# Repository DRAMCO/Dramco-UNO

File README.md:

# Dramco UNO

LoRaWAN-enabled Arduino board developed by [DRAMCO](https://www.dramco.be) featuring an accelerometer and a onewire connection optimized for low-power.

## Folder Structure

```
├───app
│   ├───Accelero-Test
│   ├───Dramco-UNO
│   └───Temprature-Sensor-Test
├───hardware
└───libraries
    └───arduino-lmic-master
```

- Example applications can be found in `app`
- Hardware folder includes the schematics 
- Altered libraries can be found in the `libraries`folder

## Description

- The device sends temperature, accelerometer and the battery level each MEASURE_INTERVAL.
- The (onewire) temperature sensor needs to be connected to the TEMP_BUS pin
- The (I2C) accelerometer with id ACC_ID is accessed through the Wire.h library
- The battery level is measured through the readVcc() function
- The measurements sent by the node are formatted with the Cayenne Low Power Payload (https://github.com/myDevicesIoT/cayenne-docs/blob/master/docs/LORA.md)

##  Dependencies:
- OneWire lib
- DallasTemperature lib
- Install arduino-lmic-master in lib folder of the Arduino IDE (for windows this is most likely here: C:\Program Files (x86)\Arduino\libraries)
    * If you do not use the lib provided in this repo, be sure to uncomment '#define DISABLE_JOIN' in src>lmic>config.h
- DeepSleepScheduler lib

- LoRaWAN keys see: https://www.thethingsnetwork.org/docs/devices/registration.html

## How to cite
```LaTex
@Misc{Dramco-UNO,
  author =   {B. Thoen and G. Leenders},
  title =    {{Dramco UNO}},
  howpublished  = "\url{https://github.com/DRAMCO/Dramco-UNO}",
  doi = {10.5281/zenodo.2476999}
}
```

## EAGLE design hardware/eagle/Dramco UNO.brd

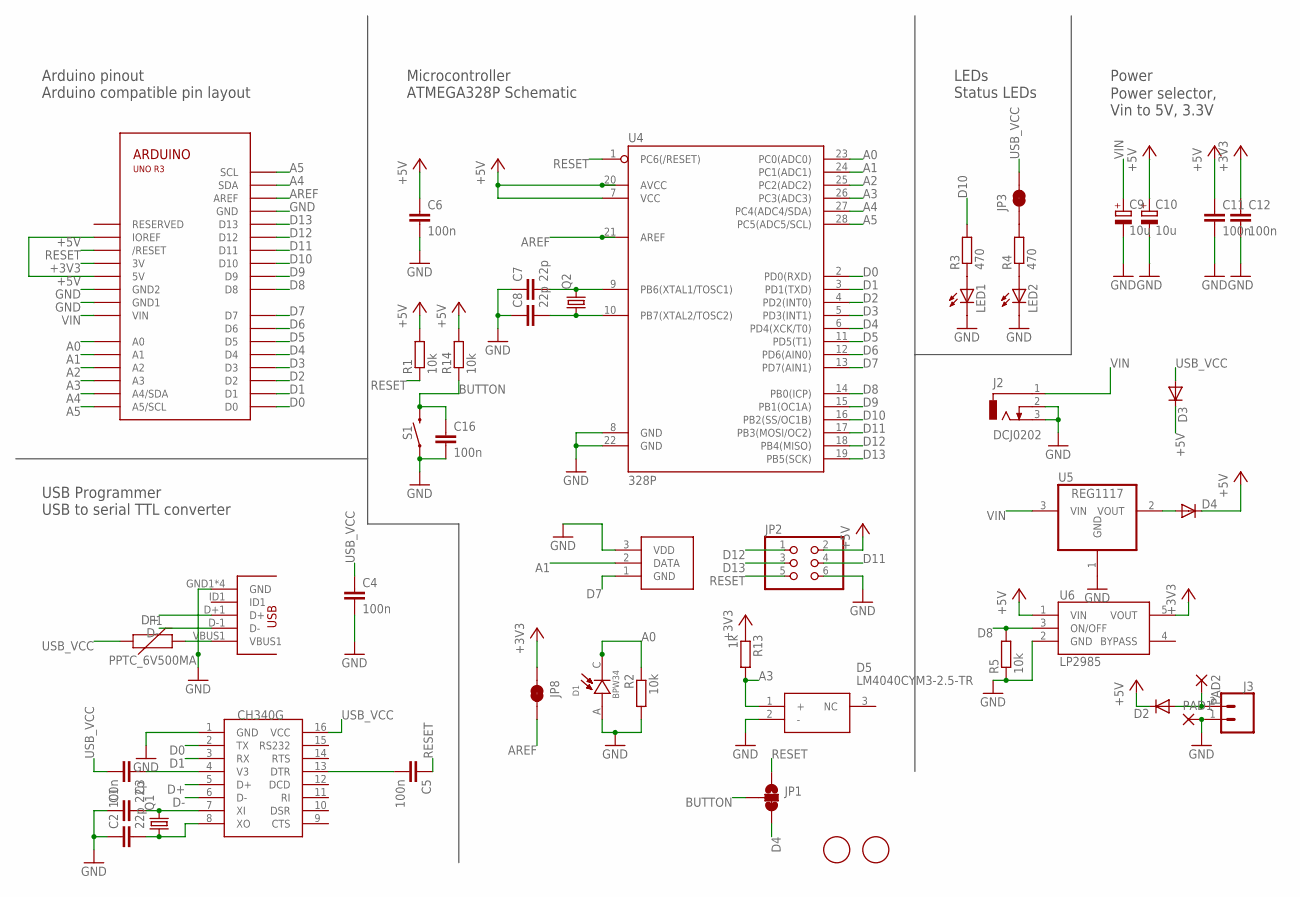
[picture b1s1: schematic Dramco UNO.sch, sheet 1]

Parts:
C1, C2, C7, C8: 22p; C025-024X044
C3, C4, C5, C11, C12, C16: 100n; C0603
C6: 100n; C025-024X044
C9, C10: 10u; E2-4
D1: BPW34; DIO_BPW34
D2, D3, D4: DIODE-D-5; D-5
D5: LM4040CYM3-2.5-TR; SOT95P235X111-3N
F1: PPTC_6V500MA; 0805
J1: USB-AB; USB-AB-MICRO-SMD_V02_BOSS
J2: DCJ0202
J3: CONN_02JST-PTH-2; JST-2-PTH
JP1: JUMPER-SMT_3_1-NC_TRACE_SILK; SMT-JUMPER_3_1-NC_TRACE_SILK
JP2: PINHD-2X3; 2X03
JP3, JP8: JUMPER-SMT_2_NC_TRACE_NO-SILK; SMT-JUMPER_2_NC_TRACE_NO-SILK
LED1, LED2: LED5MM
PAD1, PAD2: SMD2; SMD1,27-2,54
Q1, Q2: CRYSTALHC49S; HC49/S
R1, R2: 10k; 0204/7
R3, R4: 470; 0204/7
R5, R14: 10k; R0603
R13: 1k; R0603
S1: MOMENTARY-SWITCH-SPST-PTH-6.0MM; TACTILE_SWITCH_PTH_6.0MM
U1: ARDUINOR3-DIMENSION; ARDUINOR3
U2: CH340G; SOIC16
U3: DS18B20-TO92; TO92-
U4: 328P; DIP28
U5: REG1117; SOT223
U6: LP2985AIM5-3.3; SOT25
X1, X2: FIDUCIAL; FIDUCIAL_1MM

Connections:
+3V3: C12.1, JP8.1, R13.1, U1.3V, U6.5 (VOUT); also elsewhere on the board
+5V: C6.1, C10.+, C11.1, D2.C, D3.C, D4.C, JP2.2, R1.2, R14.2, U1.5V, U1.IOREF, U4.7 (VCC), U4.20 (AVCC), U6.1 (VIN); also elsewhere on the board
A0: D1.C, R2.1, U1.A0, U4.23 (PC0(ADC0))
A1: U1.A1, U3.2 (DATA), U4.24 (PC1(ADC1))
A2: U1.A2, U4.25 (PC2(ADC2))
A3: D5.1 (+), R13.2, U1.A3, U4.26 (PC3(ADC3))
A4: U1.A4 (A4/SDA), U1.SDA, U4.27 (PC4(ADC4/SDA)); also elsewhere on the board
A5: U1.A5 (A5/SCL), U1.SCL, U4.28 (PC5(ADC5/SCL)); also elsewhere on the board
AREF: JP8.2, U1.AREF, U4.21 (AREF)
BUTTON: C16.1, JP1.2, R14.1, S1.3 (2)
D0: U1.D0, U2.2 (TX), U4.2 (PD0(RXD))
D1: U1.D1, U2.3 (RX), U4.3 (PD1(TXD))
D2: U1.D2, U4.4 (PD2(INT0)); also elsewhere on the board
D3: U1.D3, U4.5 (PD3(INT1)); also elsewhere on the board
D4: JP1.3, U1.D4, U4.6 (PD4(XCK/T0)); also elsewhere on the board
D5: U1.D5, U4.11 (PD5(T1)); also elsewhere on the board
D6: U1.D6, U4.12 (PD6(AIN0)); also elsewhere on the board
D7: U1.D7, U3.1 (GND), U4.13 (PD7(AIN1))
D8: R5.2, U1.D8, U4.14 (PB0(ICP)), U6.3 (ON/OFF)
D9: U1.D9, U4.15 (PB1(OC1A)); also elsewhere on the board
D10: R3.2, U1.D10, U4.16 (PB2(SS/OC1B))
D11: JP2.4, U1.D11, U4.17 (PB3(MOSI/OC2)); also elsewhere on the board
D12: JP2.1, U1.D12, U4.18 (PB4(MISO)); also elsewhere on the board
D13: JP2.3, U1.D13, U4.19 (PB5(SCK)); also elsewhere on the board
D+: J1.D+1 (D+), U2.5 (D+)
D-: J1.D-1 (D-), U2.6 (D-)
GND: C1.1, C2.1, C4.2, C6.2, C7.1, C8.1, C9.-, C10.-, C11.2, C12.2, C16.2, D1.A, D5.2 (-), J1.GND1 (GND), J1.P$1 (GND), J1.P$2 (GND), J1.P$3 (GND), J2.2, J2.3, J3.1, JP2.6, LED1.K (C), LED2.K (C), PAD1.1, R2.2, R5.1, S1.1, U1.GND, U1.GND1, U1.GND2, U2.1 (GND), U3.3 (VDD), U4.8 (GND), U4.22 (GND), U5.1 (GND), U6.2 (GND); also elsewhere on the board
unnamed: C7.2, Q2.2, U4.9 (PB6(XTAL1/TOSC1))
unnamed: C8.2, Q2.1, U4.10 (PB7(XTAL2/TOSC2))
unnamed: C1.2, Q1.2, U2.7 (XI)
unnamed: C2.2, Q1.1, U2.8 (XO)
unnamed: C3.1, U2.4 (V3)
unnamed: LED1.A, R3.1
unnamed: LED2.A, R4.1
unnamed: C5.2, U2.13 (DTR)
unnamed: D4.A, U5.2 (VOUT)
unnamed: F1.2, J1.VBUS1
unnamed: JP3.1, R4.2
RESET: C5.1, JP1.1, JP2.5, R1.1, U1.RESET (/RESET), U4.1 (PC6(/RESET))
USB_VCC: C3.2, C4.1, D3.A, F1.1, JP3.2, U2.16 (VCC)
VBAT: D2.A, J3.2, PAD2.1
VIN: C9.+, J2.1, U1.VIN, U5.3 (VIN)

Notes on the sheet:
Arduino pinout
Arduino compatible pin layout
Microcontroller
ATMEGA328P Schematic
USB Programmer
USB to serial TTL converter
LEDs
Status LEDs
Power
Power selector, Vin to 5V, 3.3V

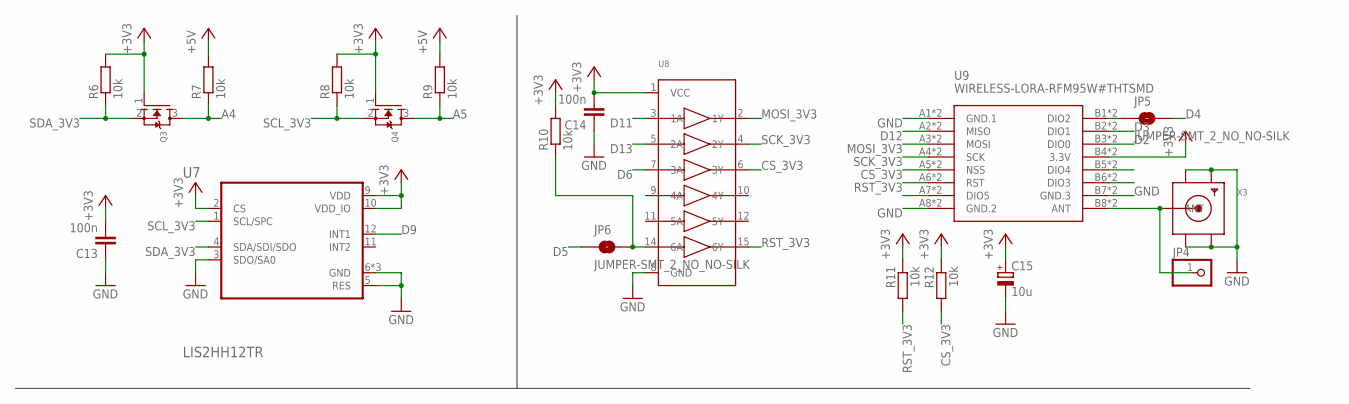
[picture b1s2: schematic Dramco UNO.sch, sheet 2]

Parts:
C13, C14: 100n; C0603
C15: 10u; E2-4
JP4: PINHD-1X1; 1X01
JP5, JP6: JUMPER-SMT_2_NO_NO-SILK; SMT-JUMPER_2_NO_NO-SILK
Q3, Q4: MOSFET-NREFLOW; SOT23
R6, R7, R8, R9, R10: 10k; R0603
R11, R12: 10k; 0204/7
U7: LIS2HH12TR; PQFN50P200X200X100-12N
U8: 74HC4050DTSSOP; TSSOP16
U9: WIRELESS-LORA-RFM95W#THTSMD
X3: SMACONNECTOR_EDGE_UFL; SMA_EDGELAUNCH_UFL

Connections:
+3V3: C13.2, C14.2, C15.+, Q3.1 (G), Q4.1 (G), R6.2, R8.2, R10.2, R11.1, R12.1, U7.2 (CS), U7.9 (VDD), U7.10 (VDD_IO), U8.1 (VCC), U9.B4 (3.3V), U9.B12 (3.3V); also elsewhere on the board
+5V: R7.2, R9.2; also elsewhere on the board
A4: Q3.3 (D), R7.1; also elsewhere on the board
A5: Q4.3 (D), R9.1; also elsewhere on the board
CS_3V3: R12.2, U8.6 (3Y), U9.A5 (NSS), U9.A13 (NSS)
D2: U9.B3 (DIO0), U9.B11 (DIO0); also elsewhere on the board
D3: U9.B2 (DIO1), U9.B10 (DIO1); also elsewhere on the board
D4: JP5.2; also elsewhere on the board
D5: JP6.1; also elsewhere on the board
D6: U8.7 (3A); also elsewhere on the board
D9: U7.12 (INT1); also elsewhere on the board
D11: U8.3 (1A); also elsewhere on the board
D12: U9.A2 (MISO), U9.A10 (MISO); also elsewhere on the board
D13: U8.5 (2A); also elsewhere on the board
GND: C13.1, C14.1, C15.-, U7.3 (SDO/SA0), U7.5 (RES), U7.6 (GND), U7.7 (GND), U7.8 (GND), U8.8 (GND), U9.A1 (GND.1), U9.A8 (GND.2), U9.A9 (GND.1), U9.A16 (GND.2), U9.B7 (GND.3), U9.B15 (GND.3), X3.GND@1 (GND1), X3.GND@2 (GND2), X3.GND@3 (GND3), X3.GND@4 (GND4); also elsewhere on the board
MOSI_3V3: U8.2 (1Y), U9.A3 (MOSI), U9.A11 (MOSI)
unnamed: JP4.1, U9.B8 (ANT), U9.B16 (ANT), X3.P (ANT)
unnamed: JP5.1, U9.B1 (DIO2), U9.B9 (DIO2)
unnamed: JP6.2, R10.1, U8.14 (6A)
unnamed: U9.A7 (DIO5), U9.A15 (DIO5)
unnamed: U9.B5 (DIO4), U9.B13 (DIO4)
unnamed: U9.B6 (DIO3), U9.B14 (DIO3)
RST_3V3: R11.2, U8.15 (6Y), U9.A6 (RST), U9.A14 (RST)
SCK_3V3: U8.4 (2Y), U9.A4 (SCK), U9.A12 (SCK)
SCL_3V3: Q4.2 (S), R8.1, U7.1 (SCL/SPC)
SDA_3V3: Q3.2 (S), R6.1, U7.4 (SDA/SDI/SDO)

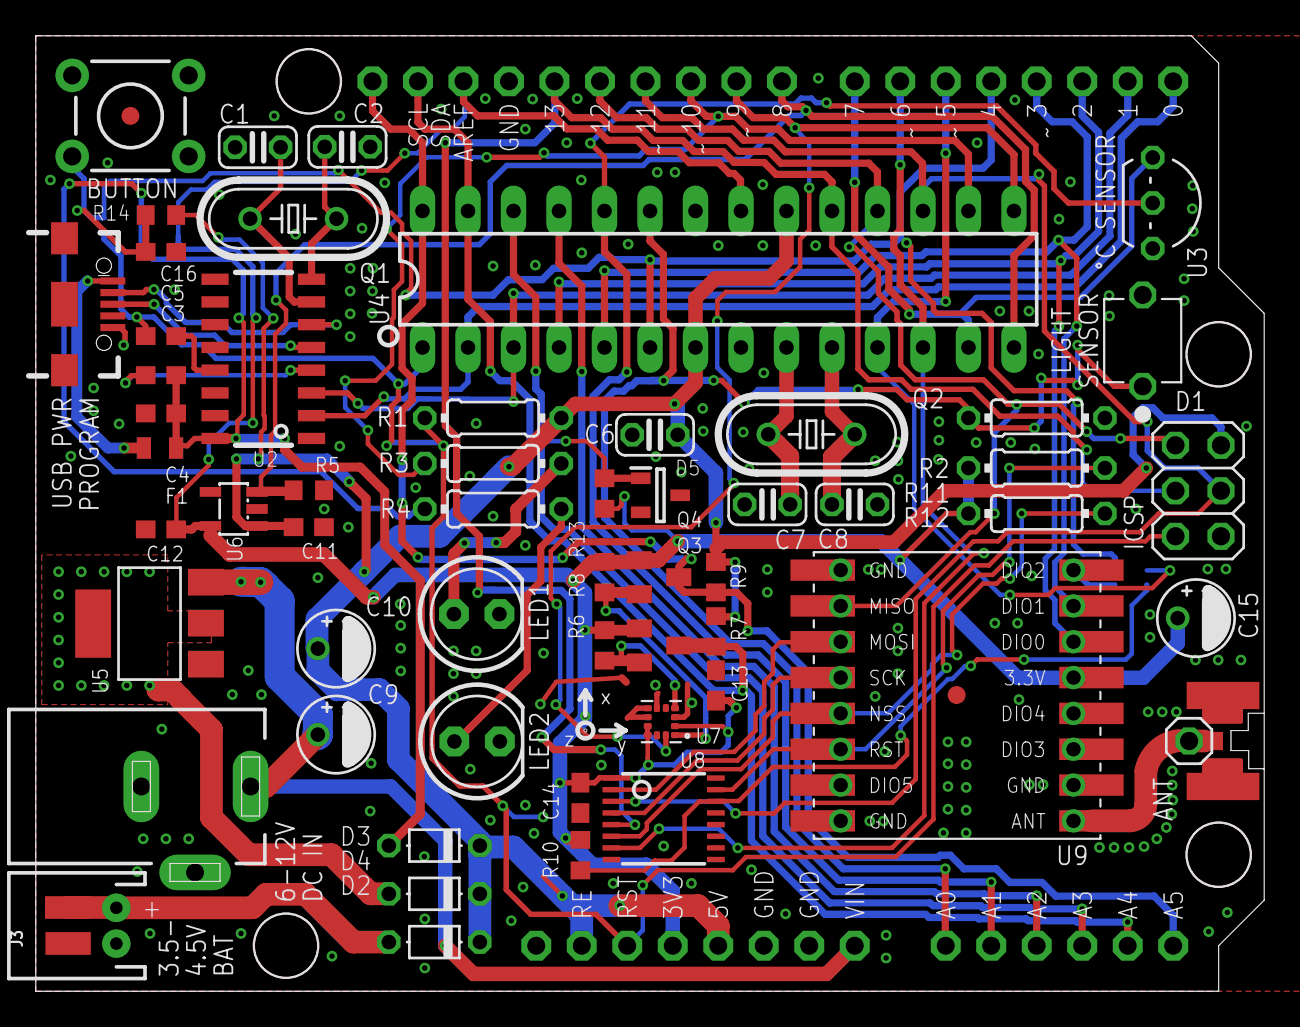
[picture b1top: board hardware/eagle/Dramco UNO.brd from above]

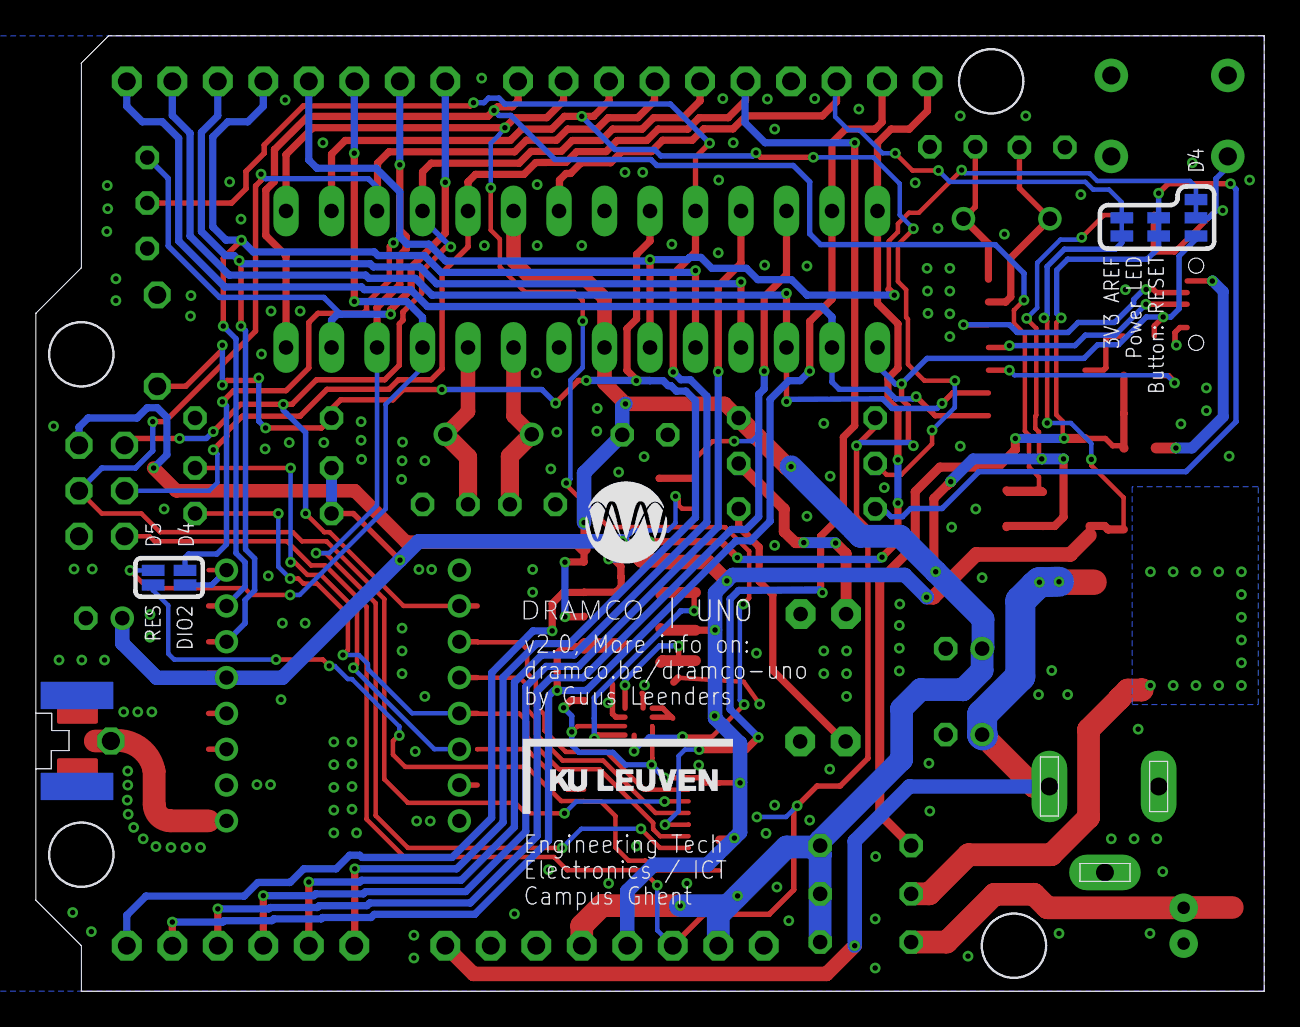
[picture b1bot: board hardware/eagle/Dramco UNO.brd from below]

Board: 2 copper layers, 68.5 x 53.2 mm, 67 parts (5 on the bottom side), 54 nets.

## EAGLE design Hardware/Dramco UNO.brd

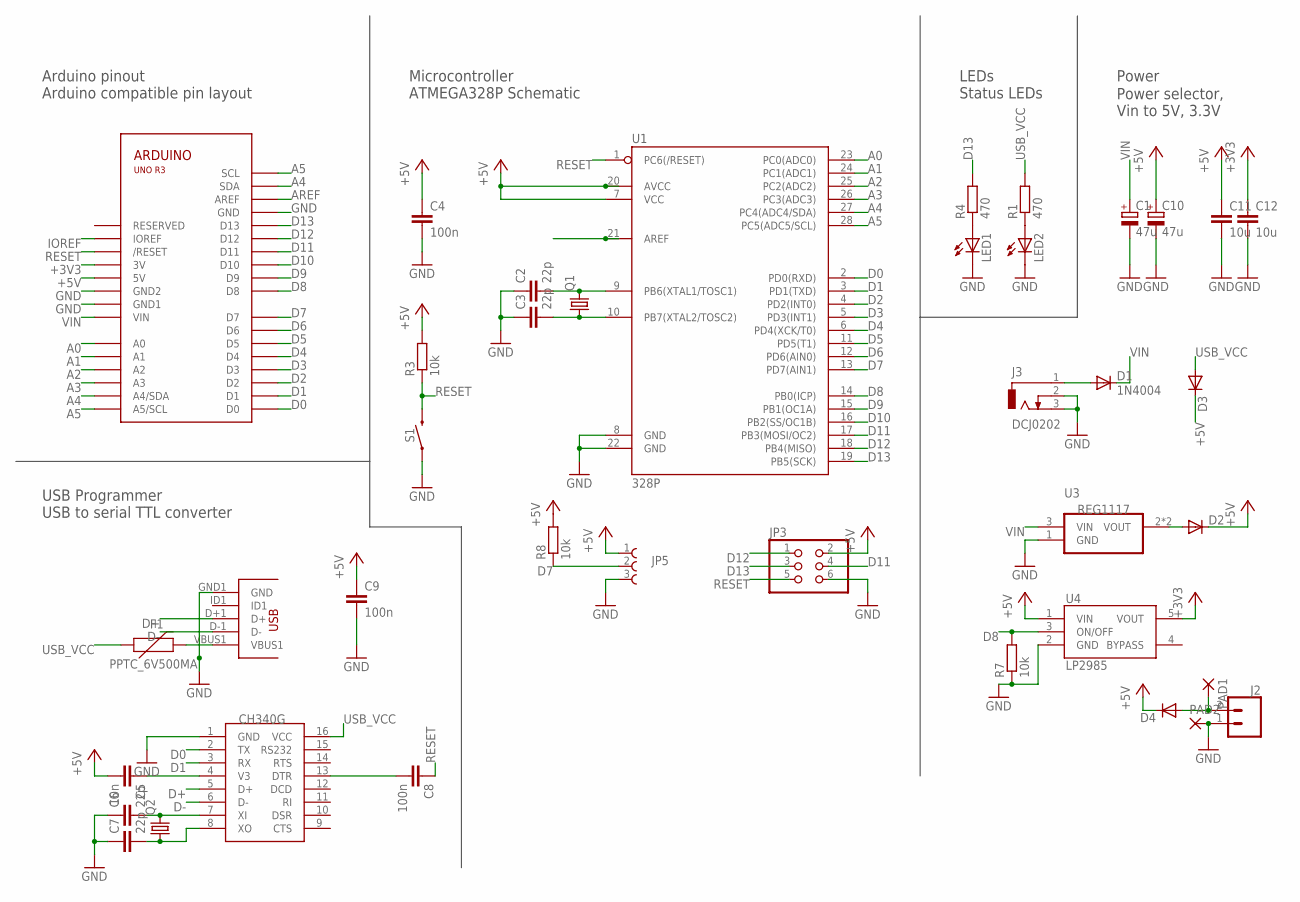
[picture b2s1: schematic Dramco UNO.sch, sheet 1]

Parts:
C1, C10: 47u; E2,5-6
C2, C3: 22p; C025-024X044
C4: 100n; C025-024X044
C5: 10n; C0603
C6, C7: 22p; C0603
C8, C9: 100n; C0603
C11, C12: 10u; C0603
D1: 1N4004; DO41-10
D2, D3, D4: DIODE-SOD123; SOD123
F1: PPTC_6V500MA; 0805
J1: USB-AB; USB-AB-MICRO-SMD_V02_BOSS
J2: CONN_02JST-PTH-2; JST-2-PTH
J3: DCJ0202
JP1: ARDUINOR3-DIMENSION; ARDUINOR3
JP3: PINHD-2X3; 2X03
JP5: 691210910003
LED1, LED2: LED5MM
PAD1, PAD2: SMD2; SMD1,27-2,54
Q1, Q2: CRYSTALHC49S; HC49/S
R1, R4: 470; 0204/7
R3, R8: 10k; 0204/7
R7: 10k; R0603
S1: MOMENTARY-SWITCH-SPST-PTH-6.0MM; TACTILE_SWITCH_PTH_6.0MM
U1: 328P; DIP28
U2: CH340G; SOIC16
U3: REG1117; SOT223
U4: LP2985AIM5-3.3; SOT25

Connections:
+3V3: C12.1, JP1.3V, U4.5 (VOUT); also elsewhere on the board
+5V: C4.1, C5.2, C9.1, C10.+, C11.1, D2.C, D3.C, D4.C, JP1.5V, JP3.2, JP5.1, R3.2, R8.2, U1.7 (VCC), U1.20 (AVCC), U4.1 (VIN); also elsewhere on the board
A0: JP1.A0, U1.23 (PC0(ADC0))
A1: JP1.A1, U1.24 (PC1(ADC1))
A2: JP1.A2, U1.25 (PC2(ADC2))
A3: JP1.A3, U1.26 (PC3(ADC3))
A4: JP1.A4 (A4/SDA), JP1.SDA, U1.27 (PC4(ADC4/SDA)); also elsewhere on the board
A5: JP1.A5 (A5/SCL), JP1.SCL, U1.28 (PC5(ADC5/SCL)); also elsewhere on the board
AREF: JP1.AREF, U1.21 (AREF)
D0: JP1.D0, U1.2 (PD0(RXD)), U2.2 (TX)
D1: JP1.D1, U1.3 (PD1(TXD)), U2.3 (RX)
D2: JP1.D2, U1.4 (PD2(INT0)); also elsewhere on the board
D3: JP1.D3, U1.5 (PD3(INT1)); also elsewhere on the board
D4: JP1.D4, U1.6 (PD4(XCK/T0)); also elsewhere on the board
D5: JP1.D5, U1.11 (PD5(T1)); also elsewhere on the board
D6: JP1.D6, U1.12 (PD6(AIN0)); also elsewhere on the board
D7: JP1.D7, JP5.2, R8.1, U1.13 (PD7(AIN1))
D8: JP1.D8, R7.2, U1.14 (PB0(ICP)), U4.3 (ON/OFF)
D9: JP1.D9, U1.15 (PB1(OC1A)); also elsewhere on the board
D10: JP1.D10, U1.16 (PB2(SS/OC1B))
D11: JP1.D11, JP3.4, U1.17 (PB3(MOSI/OC2)); also elsewhere on the board
D12: JP1.D12, JP3.1, U1.18 (PB4(MISO)); also elsewhere on the board
D13: JP1.D13, JP3.3, R4.2, U1.19 (PB5(SCK)); also elsewhere on the board
D+: J1.D+1 (D+), U2.5 (D+)
D-: J1.D-1 (D-), U2.6 (D-)
GND: C1.-, C2.1, C3.1, C4.2, C6.1, C7.1, C9.2, C10.-, C11.2, C12.2, J1.GND1 (GND), J2.1, J3.2, J3.3, JP1.GND, JP1.GND1, JP1.GND2, JP3.6, JP5.3, LED1.K (C), LED2.K (C), PAD2.1, R7.1, S1.1, U1.8 (GND), U1.22 (GND), U2.1 (GND), U3.1 (GND), U4.2 (GND); also elsewhere on the board
IOREF: JP1.IOREF
unnamed: C2.2, Q1.2, U1.9 (PB6(XTAL1/TOSC1))
unnamed: C3.2, Q1.1, U1.10 (PB7(XTAL2/TOSC2))
unnamed: C6.2, Q2.2, U2.7 (XI)
unnamed: C7.2, Q2.1, U2.8 (XO)
unnamed: C5.1, U2.4 (V3)
unnamed: LED1.A, R4.1
unnamed: LED2.A, R1.1
unnamed: C8.2, U2.13 (DTR)
unnamed: D2.A, U3.2 (VOUT), U3.4 (VOUT)
unnamed: F1.2, J1.VBUS1
unnamed: D1.A, J3.1
RESET: C8.1, JP1.RESET (/RESET), JP3.5, R3.1, S1.3 (2), U1.1 (PC6(/RESET))
USB_VCC: D3.A, F1.1, R1.2, U2.16 (VCC)
VBAT: D4.A, J2.2, PAD1.1
VIN: C1.+, D1.C, JP1.VIN, U3.3 (VIN)

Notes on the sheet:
Arduino pinout
Arduino compatible pin layout
Microcontroller
ATMEGA328P Schematic
USB Programmer
USB to serial TTL converter
LEDs
Status LEDs
Power
Power selector, Vin to 5V, 3.3V

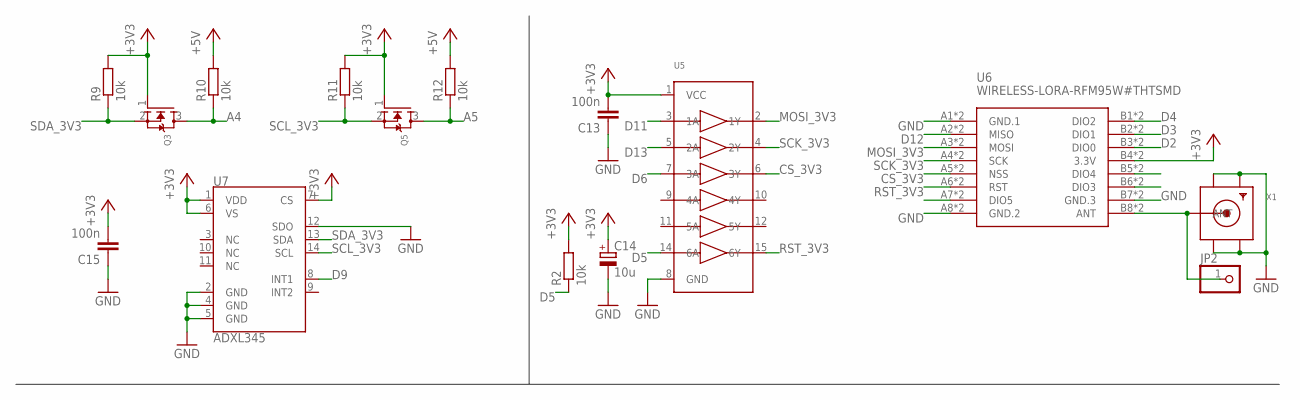
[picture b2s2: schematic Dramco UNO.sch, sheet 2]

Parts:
C13, C15: 100n; C0603
C14: 10u; E2-4
JP2: PINHD-1X1; 1X01
Q3, Q5: MOSFET-NREFLOW; SOT23
R2, R9, R10, R11, R12: 10k; R0603
U5: 74HC4050DTSSOP; TSSOP16
U6: WIRELESS-LORA-RFM95W#THTSMD
U7: ADXL345; LGA-14
X1: SMACONNECTOR_EDGE_UFL; SMA_EDGELAUNCH_UFL

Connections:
+3V3: C13.2, C14.+, C15.2, Q3.1 (G), Q5.1 (G), R2.2, R9.2, R11.2, U5.1 (VCC), U6.B4 (3.3V), U6.B12 (3.3V), U7.1 (VDD), U7.6 (VS), U7.7 (CS); also elsewhere on the board
+5V: R10.2, R12.2; also elsewhere on the board
A4: Q3.3 (D), R10.1; also elsewhere on the board
A5: Q5.3 (D), R12.1; also elsewhere on the board
CS_3V3: U5.6 (3Y), U6.A5 (NSS), U6.A13 (NSS)
D2: U6.B3 (DIO0), U6.B11 (DIO0); also elsewhere on the board
D3: U6.B2 (DIO1), U6.B10 (DIO1); also elsewhere on the board
D4: U6.B1 (DIO2), U6.B9 (DIO2); also elsewhere on the board
D5: R2.1, U5.14 (6A); also elsewhere on the board
D6: U5.7 (3A); also elsewhere on the board
D9: U7.8 (INT1); also elsewhere on the board
D11: U5.3 (1A); also elsewhere on the board
D12: U6.A2 (MISO), U6.A10 (MISO); also elsewhere on the board
D13: U5.5 (2A); also elsewhere on the board
GND: C13.1, C14.-, C15.1, U5.8 (GND), U6.A1 (GND.1), U6.A8 (GND.2), U6.A9 (GND.1), U6.A16 (GND.2), U6.B7 (GND.3), U6.B15 (GND.3), U7.2 (GND), U7.4 (GND), U7.5 (GND), U7.12 (SDO), X1.GND@1 (GND1), X1.GND@2 (GND2), X1.GND@3 (GND3), X1.GND@4 (GND4); also elsewhere on the board
MOSI_3V3: U5.2 (1Y), U6.A3 (MOSI), U6.A11 (MOSI)
unnamed: JP2.1, U6.B8 (ANT), U6.B16 (ANT), X1.P (ANT)
unnamed: U6.A7 (DIO5), U6.A15 (DIO5)
unnamed: U6.B5 (DIO4), U6.B13 (DIO4)
unnamed: U6.B6 (DIO3), U6.B14 (DIO3)
RST_3V3: U5.15 (6Y), U6.A6 (RST), U6.A14 (RST)
SCK_3V3: U5.4 (2Y), U6.A4 (SCK), U6.A12 (SCK)
SCL_3V3: Q5.2 (S), R11.1, U7.14 (SCL)
SDA_3V3: Q3.2 (S), R9.1, U7.13 (SDA)

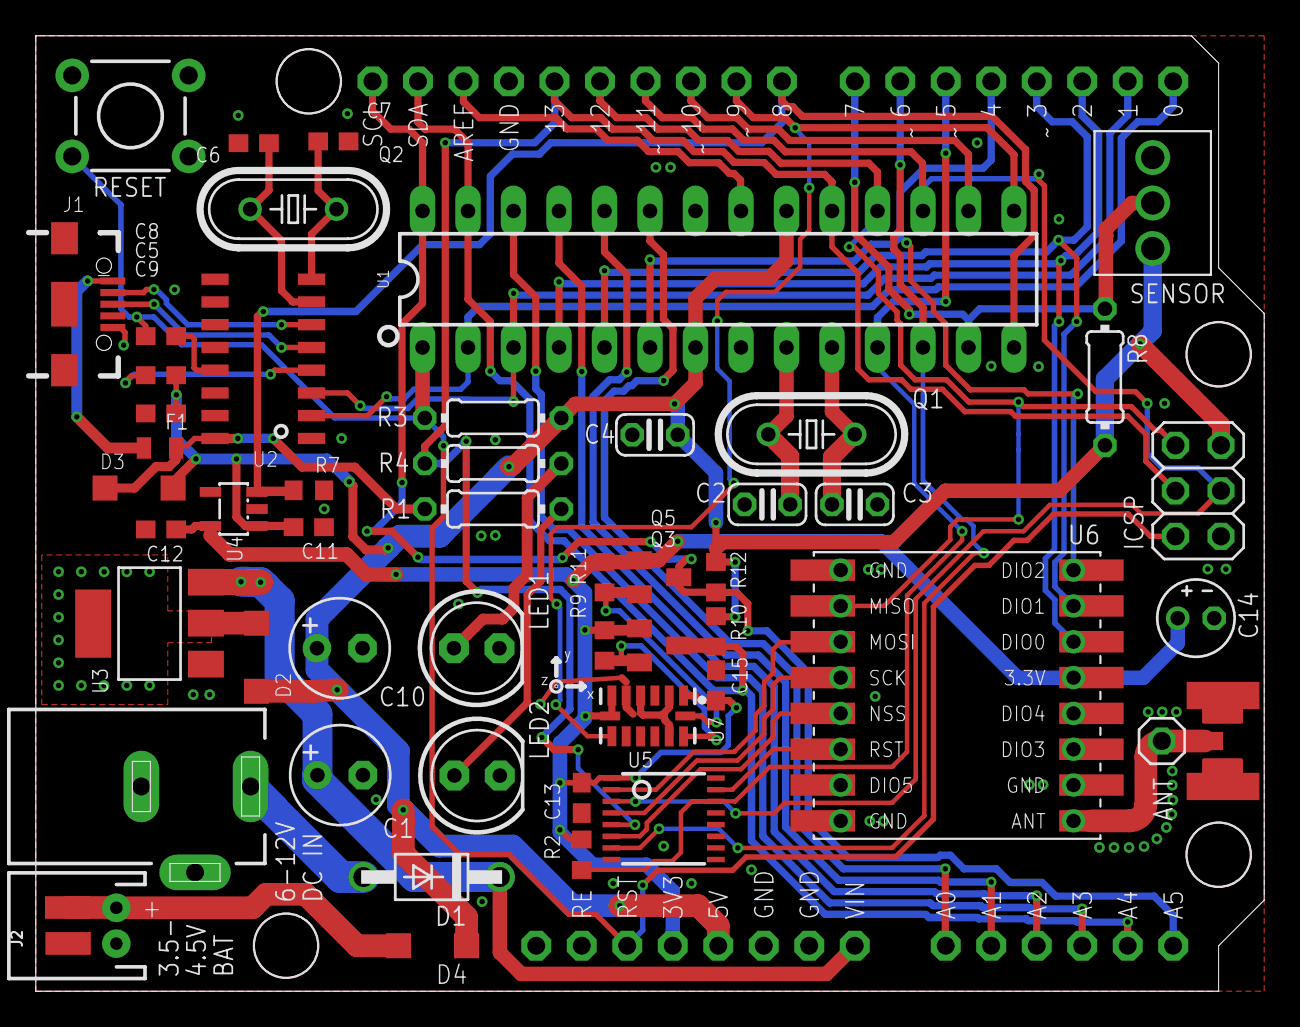
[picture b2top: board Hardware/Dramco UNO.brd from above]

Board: 2 copper layers, 68.5 x 53.2 mm, 54 parts (0 on the bottom side), 51 nets.

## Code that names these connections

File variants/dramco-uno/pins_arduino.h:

/*
  pins_arduino.h - Pin definition functions for Arduino
  Part of Arduino - http://www.arduino.cc/

  Copyright (c) 2007 David A. Mellis

  This library is free software; you can redistribute it and/or
  modify it under the terms of the GNU Lesser General Public
  License as published by the Free Software Foundation; either
  version 2.1 of the License, or (at your option) any later version.

  This library is distributed in the hope that it will be useful,
  but WITHOUT ANY WARRANTY; without even the implied warranty of
  MERCHANTABILITY or FITNESS FOR A PARTICULAR PURPOSE.  See the GNU
  Lesser General Public License for more details.

  You should have received a copy of the GNU Lesser General
  Public License along with this library; if not, write to the
  Free Software Foundation, Inc., 59 Temple Place, Suite 330,
  Boston, MA  02111-1307  USA
*/

#ifndef Pins_Arduino_h
#define Pins_Arduino_h

#include <avr/pgmspace.h>

#define NUM_DIGITAL_PINS            20
#define NUM_ANALOG_INPUTS           6
#define analogInputToDigitalPin(p)  ((p < 6) ? (p) + 14 : -1)

#if defined(__AVR_ATmega8__)
#define digitalPinHasPWM(p)         ((p) == 9 || (p) == 10 || (p) == 11)
#else
#define digitalPinHasPWM(p)         ((p) == 3 || (p) == 5 || (p) == 6 || (p) == 9 || (p) == 10 || (p) == 11)
#endif

#define PIN_SPI_SS    (10)
#define PIN_SPI_MOSI  (11)
#define PIN_SPI_MISO  (12)
#define PIN_SPI_SCK   (13)

static const uint8_t SS   = PIN_SPI_SS;
static const uint8_t MOSI = PIN_SPI_MOSI;
static const uint8_t MISO = PIN_SPI_MISO;
static const uint8_t SCK  = PIN_SPI_SCK;

#define PIN_WIRE_SDA        (18)
#define PIN_WIRE_SCL        (19)

static const uint8_t SDA = PIN_WIRE_SDA;
static const uint8_t SCL = PIN_WIRE_SCL;

#if HARDWARE_VERSION >= 2
#define LED_BUILTIN 10
#else
#define LED_BUILTIN 4
#endif

#define PIN_A0   (14)
#define PIN_A1   (15)
#define PIN_A2   (16)
#define PIN_A3   (17)
#define PIN_A4   (18)
#define PIN_A5   (19)
#define PIN_A6   (20)
#define PIN_A7   (21)

static const uint8_t A0 = PIN_A0;
static const uint8_t A1 = PIN_A1;
static const uint8_t A2 = PIN_A2;
static const uint8_t A3 = PIN_A3;
static const uint8_t A4 = PIN_A4;
static const uint8_t A5 = PIN_A5;
static const uint8_t A6 = PIN_A6;
static const uint8_t A7 = PIN_A7;

#define digitalPinToPCICR(p)    (((p) >= 0 && (p) <= 21) ? (&PCICR) : ((uint8_t *)0))
#define digitalPinToPCICRbit(p) (((p) <= 7) ? 2 : (((p) <= 13) ? 0 : 1))
#define digitalPinToPCMSK(p)    (((p) <= 7) ? (&PCMSK2) : (((p) <= 13) ? (&PCMSK0) : (((p) <= 21) ? (&PCMSK1) : ((uint8_t *)0))))
#define digitalPinToPCMSKbit(p) (((p) <= 7) ? (p) : (((p) <= 13) ? ((p) - 8) : ((p) - 14)))

#define digitalPinToInterrupt(p)  ((p) == 2 ? 0 : ((p) == 3 ? 1 : NOT_AN_INTERRUPT))

#ifdef ARDUINO_MAIN

// On the Arduino board, digital pins are also used
// for the analog output (software PWM).  Analog input
// pins are a separate set.

// ATMEL ATMEGA8 & 168 / ARDUINO
//
//                  +-\/-+
//            PC6  1|    |28  PC5 (AI 5)
//      (D 0) PD0  2|    |27  PC4 (AI 4)
//      (D 1) PD1  3|    |26  PC3 (AI 3)
//      (D 2) PD2  4|    |25  PC2 (AI 2)
// PWM+ (D 3) PD3  5|    |24  PC1 (AI 1)
//      (D 4) PD4  6|    |23  PC0 (AI 0)
//            VCC  7|    |22  GND
//            GND  8|    |21  AREF
//            PB6  9|    |20  AVCC
//            PB7 10|    |19  PB5 (D 13)
// PWM+ (D 5) PD5 11|    |18  PB4 (D 12)
// PWM+ (D 6) PD6 12|    |17  PB3 (D 11) PWM
//      (D 7) PD7 13|    |16  PB2 (D 10) PWM
//      (D 8) PB0 14|    |15  PB1 (D 9) PWM
//                  +----+
//
// (PWM+ indicates the additional PWM pins on the ATmega168.)

// ATMEL ATMEGA1280 / ARDUINO
//
// 0-7 PE0-PE7   works
// 8-13 PB0-PB5  works
// 14-21 PA0-PA7 works 
// 22-29 PH0-PH7 works
// 30-35 PG5-PG0 works
// 36-43 PC7-PC0 works
// 44-51 PJ7-PJ0 works
// 52-59 PL7-PL0 works
// 60-67 PD7-PD0 works
// A0-A7 PF0-PF7
// A8-A15 PK0-PK7


// these arrays map port names (e.g. port B) to the
// appropriate addresses for various functions (e.g. reading
// and writing)
const uint16_t PROGMEM port_to_mode_PGM[] = {
	NOT_A_PORT,
	NOT_A_PORT,
	(uint16_t) &DDRB,
	(uint16_t) &DDRC,
	(uint16_t) &DDRD,
};

const uint16_t PROGMEM port_to_output_PGM[] = {
	NOT_A_PORT,
	NOT_A_PORT,
	(uint16_t) &PORTB,
	(uint16_t) &PORTC,
	(uint16_t) &PORTD,
};

const uint16_t PROGMEM port_to_input_PGM[] = {
	NOT_A_PORT,
	NOT_A_PORT,
	(uint16_t) &PINB,
	(uint16_t) &PINC,
	(uint16_t) &PIND,
};

const uint8_t PROGMEM digital_pin_to_port_PGM[] = {
	PD, /* 0 */
	PD,
	PD,
	PD,
	PD,
	PD,
	PD,
	PD,
	PB, /* 8 */
	PB,
	PB,
	PB,
	PB,
	PB,
	PC, /* 14 */
	PC,
	PC,
	PC,
	PC,
	PC,
};

const uint8_t PROGMEM digital_pin_to_bit_mask_PGM[] = {
	_BV(0), /* 0, port D */
	_BV(1),
	_BV(2),
	_BV(3),
	_BV(4),
	_BV(5),
	_BV(6),
	_BV(7),
	_BV(0), /* 8, port B */
	_BV(1),
	_BV(2),
	_BV(3),
	_BV(4),
	_BV(5),
	_BV(0), /* 14, port C */
	_BV(1),
	_BV(2),
	_BV(3),
	_BV(4),
	_BV(5),
};

const uint8_t PROGMEM digital_pin_to_timer_PGM[] = {
	NOT_ON_TIMER, /* 0 - port D */
	NOT_ON_TIMER,
	NOT_ON_TIMER,
	// on the ATmega168, digital pin 3 has hardware pwm
#if defined(__AVR_ATmega8__)
	NOT_ON_TIMER,
#else
	TIMER2B,
#endif
	NOT_ON_TIMER,
	// on the ATmega168, digital pins 5 and 6 have hardware pwm
#if defined(__AVR_ATmega8__)
	NOT_ON_TIMER,
	NOT_ON_TIMER,
#else
	TIMER0B,
	TIMER0A,
#endif
	NOT_ON_TIMER,
	NOT_ON_TIMER, /* 8 - port B */
	TIMER1A,
	TIMER1B,
#if defined(__AVR_ATmega8__)
	TIMER2,
#else
	TIMER2A,
#endif
	NOT_ON_TIMER,
	NOT_ON_TIMER,
	NOT_ON_TIMER,
	NOT_ON_TIMER, /* 14 - port C */
	NOT_ON_TIMER,
	NOT_ON_TIMER,
	NOT_ON_TIMER,
	NOT_ON_TIMER,
};

#endif

// These serial port names are intended to allow libraries and architecture-neutral
// sketches to automatically default to the correct port name for a particular type
// of use.  For example, a GPS module would normally connect to SERIAL_PORT_HARDWARE_OPEN,
// the first hardware serial port whose RX/TX pins are not dedicated to another use.
//
// SERIAL_PORT_MONITOR        Port which normally prints to the Arduino Serial Monitor
//
// SERIAL_PORT_USBVIRTUAL     Port which is USB virtual serial
//
// SERIAL_PORT_LINUXBRIDGE    Port which connects to a Linux system via Bridge library
//
// SERIAL_PORT_HARDWARE       Hardware serial port, physical RX & TX pins.
//
// SERIAL_PORT_HARDWARE_OPEN  Hardware serial ports which are open for use.  Their RX & TX
//                            pins are NOT connected to anything by default.
#define SERIAL_PORT_MONITOR   Serial
#define SERIAL_PORT_HARDWARE  Serial

#endif

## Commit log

2018-06-26 Initial Upload
2018-06-26 added more test files
2018-07-04 test fils components
2018-07-04 added library lmic
2018-07-04 merging files
2018-07-04 blabla
2018-07-04 low power
2018-07-04 code cleanup
2018-07-06 dynamic temp sensors
2018-07-09 Add supply voltage measurement
2018-07-10 small changes
2018-07-10 implementing device discovery
2018-08-06 adding tempsensor identification
2018-08-07 adding temp sensor detection
2018-08-08 added sensor initphase
2018-08-09 added devices
2018-08-09 fix analog out to 0
2018-08-09 remain compatible
2018-08-10 added adresses
2018-08-14 added device ids
2018-10-03 Removed IoTree-related code and simplified the app design
2018-10-03 clean-up
2018-10-23 added how to cite
2018-11-19 Added hardware files
2018-11-20 chnage device name
2018-11-21 Added adresses workshop nodes
2018-11-27 add adresess
2018-12-21 Added folder structure
2019-01-22 fix relative dramco.be URL
    The URL to www.dramco.be is defined as a relative URL. This results in a bad link when clicking on it on Github. Changing it to an absolute URL fixes this problem.
2020-05-11 Create LICENSE
2020-09-25 Changed to board/avr structure
2020-09-25 Added example
2020-09-28 Update boards.txt
    suppress lmic project config
2020-09-28 Update DramcoUnoLib.ino
    Keys and EUIs as "LoraParam" type.
2020-09-28 Update Dramco-UNO.h
    LoraParam FTW
2020-09-28 Update Dramco-UNO.cpp
    LoraParam FTW
2020-09-29 Cleanup
2020-09-29 Added temperature and light sensor
2020-09-29 Calibration
2020-09-29 Added lpp payload for temperature
2020-09-29 Optimized lpp and added luminosity
2020-09-29 Added blink
2020-09-29 Changed build in led
2020-09-30 Implemented sleep
2020-09-30 Lowered brownout detection
    Extended fuse changed from FD to FE
2020-09-30 Sleep in blink
2020-09-30 Changed to blocking send with delay
2020-09-30 Removed OS blink, solved message bug
2020-09-30 Updated example
2020-09-30 Added temp sensor enable
2020-09-30 Added accelerometer placeholders
2020-10-01 Added license and accelerometer lib (not tested)
2020-10-01 Code optimized for memory usage
2020-10-01 Included LMIC for further memory optimizations
2020-10-01 Added package list
2020-10-02 Changed folder structure
2020-10-02 Changed license
2020-10-02 Added LPP accelerometer, fixed error
2020-10-02 Fixed accelerometer issues
2020-10-05 Disabled network time
2020-10-07 Changed pin mapping
    DIO2, reset NC; Led to 4
2020-10-07 Accelerometer working, added temp calibration
2020-10-07 Added onMotion
2020-10-07 Added pin check in int
2020-10-08 Added button
2020-10-08 Removed sendOn..
2020-10-12 Added non blocking i2c, started soil sensor
2020-10-12 Added flush before sleep
2020-10-12 Added cap discharge delay
2020-10-13 Added sendSoilMoisture
2020-10-19 Added accelerometer error function
2020-10-19 Removed low-power bug when #define DEBUG
2020-10-19 Stopped disabling pullup in sleep
2020-10-23 Changed class name to DramcoUnoClass, extern class added
2020-10-23 Changed example
2020-10-23 Added acceleromter example
2020-10-23 Removed debug
2020-10-23 Changed internal delays to sleep
2020-11-03 Fixed temperature bug
2020-11-09 Improved stability of temperature sensor
2021-02-15 Update package_dramcouno_index.json
    Updated checksum
2021-02-15 Update package_dramcouno_index.json
    Release 0.2.2
2021-02-16 Added bootloader, fixed keywords
    Thanks to Geoffrey!
2021-02-16 Disabled debug
2021-02-25 Changed default datarate to sf12
2021-02-25 Enable adr on default
2021-02-25 Improved syntax
2021-02-25 Code clean
2021-02-25 Changed default join SF to 12
2021-02-25 Added new version 0.3.2
2022-01-20 Changed to HW2 and TTNv3
2022-01-20 Changed LED_BUILTIN for v2 hardware
2022-01-20 Added hardware documentation
2022-01-20 Added pinout
2022-01-27 Fixed some warnings in libs
2022-02-18 Upgraded LMIC to latest version
2022-03-22 Serial output bug fixes
2023-03-08 Button compatibility with v1 version
2023-03-13 Light sensor compatibility with v1 version
2023-03-21 Dramco Uno V1
2023-03-21 Add ABP + light sensor fix
2023-03-22 Added version 3 support in menus
2023-03-22 Added ABP support
2023-03-22 Tried added sf selection (not tested)
2023-03-22 Fixed linker issue
2023-03-22 Added the new things to keywords
2023-03-24 Revert "Update package_dramcouno_index.json"
    This reverts commit b53b98696d870dd252b58208424c4df6b65b4543.
2023-03-24 Revert "Revert "Update package_dramcouno_index.json""
    This reverts commit 83d32ff2ea3909171678f5104df017e79c98826f.
2024-06-07 Added ENABLE_WDT option for stable dev
2024-06-07 Added counter
2025-11-21 Update Dramco-UNO.h
    Added static void _wdtEnableReset(); declaration.

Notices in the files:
parts and their libraries:
SparkFun-IC-Microcontroller: Licensing: Creative Commons ShareAlike 4.0 International - https://creativecommons.org/licenses/by-sa/4.0
diy-modules: Released under the Creative Commons Attribution 4.0 International License: http://creativecommons.org/licenses/by/4.0
